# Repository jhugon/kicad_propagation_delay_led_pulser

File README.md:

# Propagation Delay LED Pulser Board in KiCAD

This KiCad board pulses an LED with a very short pulse. The pulse width is
defined by the propagation delay of 3 inverters.

Main power supply: 5 V

LED bias: 0-1.4 V, lower is brighter

## Changelog

- v1.0 Difficult to hand-solder due to heat loss to ground plane (too many vias) and reversed 0612 capacitors
- v1.1 Remove extra vias and switch from 0612 to 1206 coupling caps

## Performance

### v1.1

Measured on 2022-05-04

Current draw not visible on power supply, so less than 10 mA

All measured with a 10x passive oscilloscope probe and ground clib hooked up to coax out:

- The clock coming out of the timer: 9.36 kHz
- The pulse coming out of the NAND gate:
  - Rise and fall times of 2 ns (may be probes)
  - Width of 11 ns
  - Baseline is 4.8 V
  - Pulse is 8 mV
- The pulse coming out of the coax driving inverters, going into R2:
  - A fair amount of ringing ~ 20%
  - Rise and fall times of 2 ns (see above)
  - Width of 11 ns
  - Baseline is -77 mV
  - Pulse is 5 V
- The LED anode:
  - Rise time: 2 ns
  - Fall time: ringing 8.5 ns
  - Width: 12 ns
  - Baseline: -77 mV
  - Pulse: 2.8 V

Pulse measurement of coax output into high-Z scope input:

- Rise time 2.48 ns
- Fall time 2.45 ns
- Width 11.61 ns
- Baseline -90 mV
- Pulse 4.6 V
- Ringing ~ 10%, damped out around 20 ns after pulse fall

LED pulse measurements return a signal as expected at 9.36 kHz. The signal is
controllable with the bias voltage. Noise seems high, but that may be something
else

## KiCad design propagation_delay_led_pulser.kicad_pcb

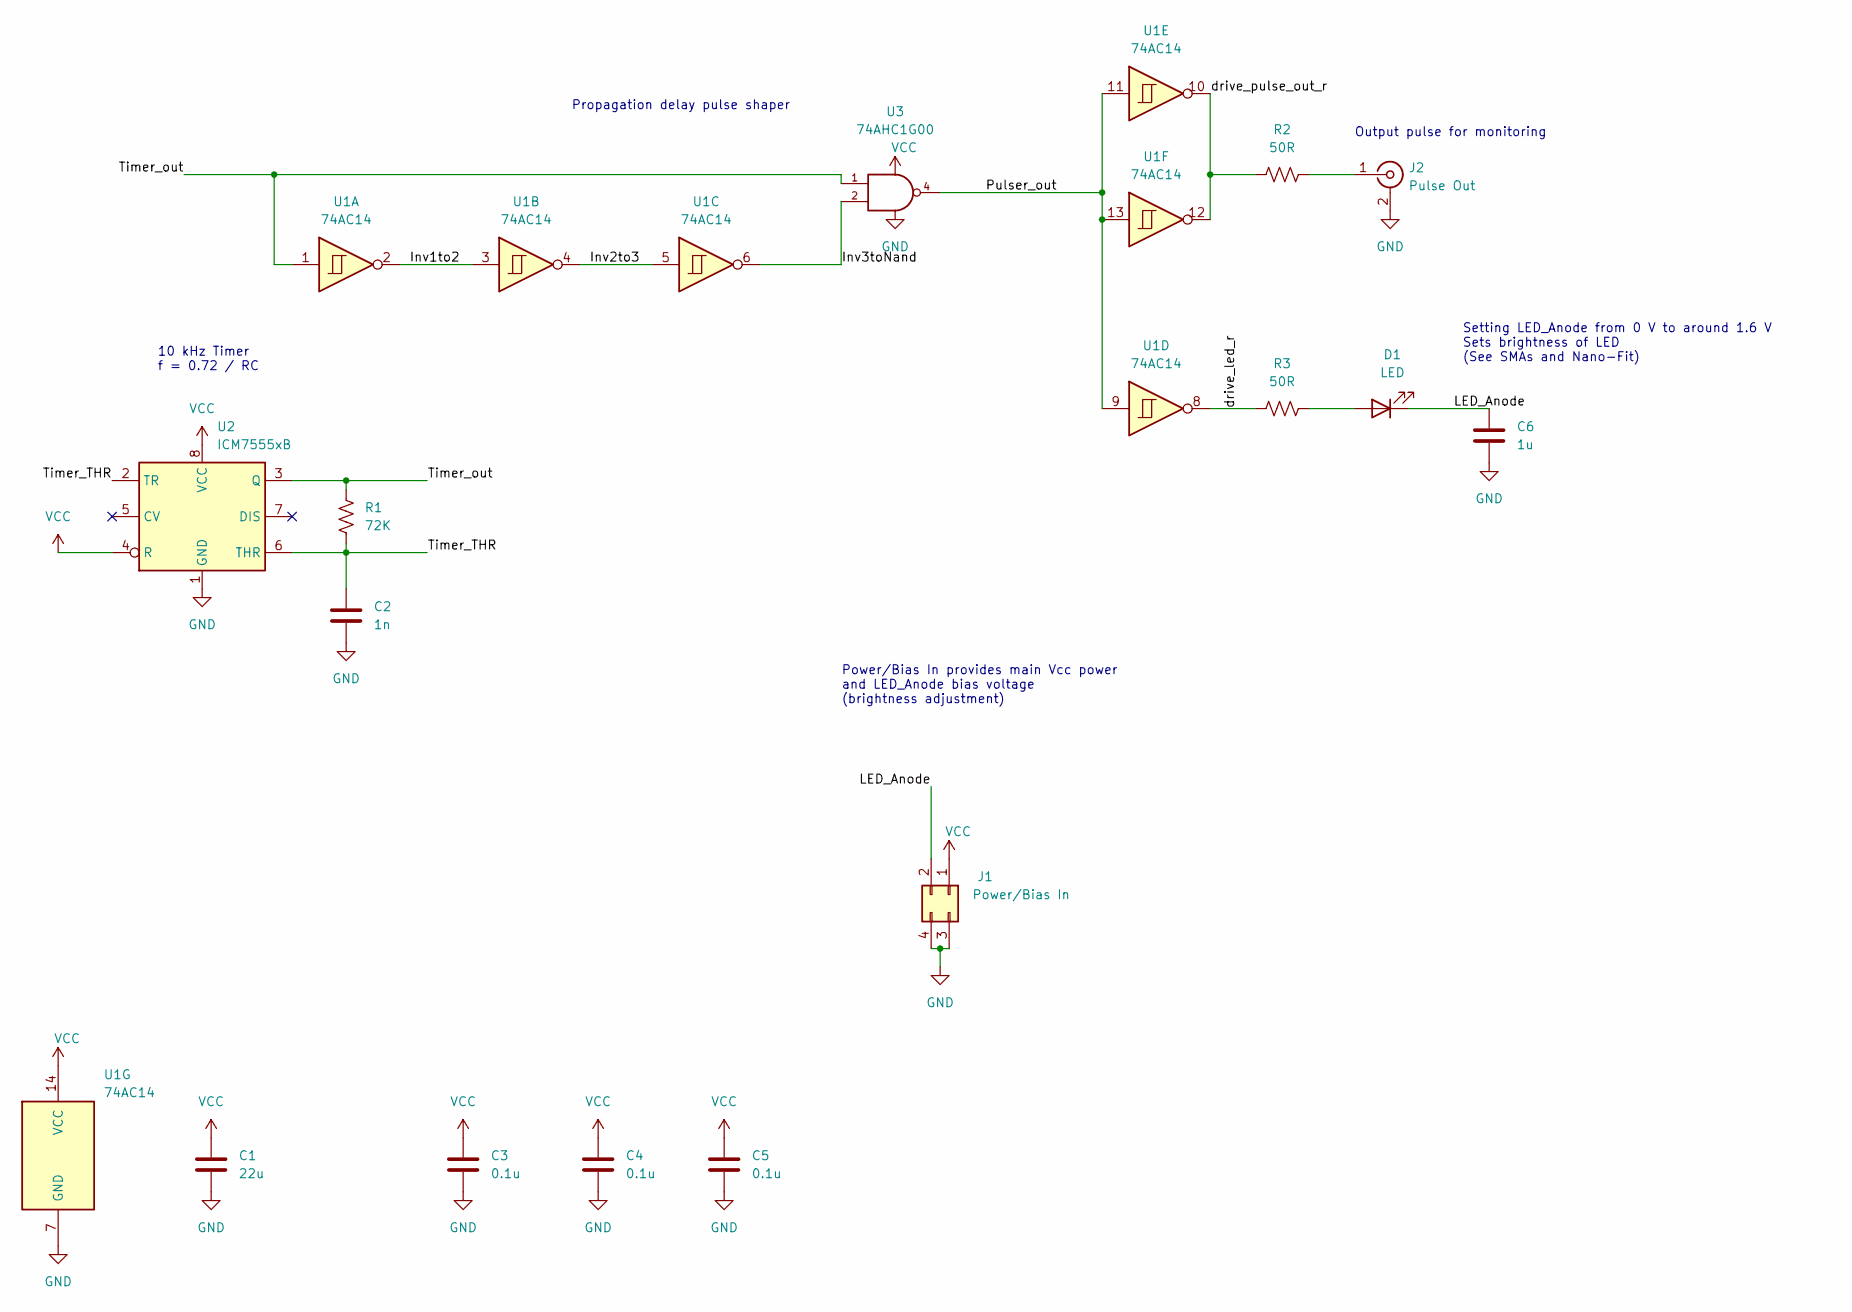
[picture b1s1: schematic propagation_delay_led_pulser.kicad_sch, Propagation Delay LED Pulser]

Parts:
C1: 22u; C_1206_3216Metric_Pad1.33x1.80mm_HandSolder; Part CL31A226KAHNNNE
C2: 1n; C_1206_3216Metric_Pad1.33x1.80mm_HandSolder; Part 12063A102FAT2A
C3, C4, C5: 0.1u; C_1206_3216Metric_Pad1.33x1.80mm_HandSolder; Part CL31B104KBCNNND
C6: 1u; C_1206_3216Metric_Pad1.33x1.80mm_HandSolder; Part CL31B105KBHNFNE
D1: LED; LED_1206_3216Metric_Pad1.42x1.75mm_HandSolder; Part LTST-C150TBKT
J1: Power/Bias In; Molex_Nano-Fit_105314-xx04_2x02_P2.50mm_Horizontal; Part 1053141304
J2: Pulse Out; SMA_Amphenol_132289_EdgeMount; Part 132289
R1: 72K; R_1206_3216Metric_Pad1.30x1.75mm_HandSolder; Part CRCW120671K5FKEA
R2, R3: 50R; R_1206_3216Metric_Pad1.30x1.75mm_HandSolder; Part CRCW120649R9FKEAC
U1: 74AC14; SOIC-14_3.9x8.7mm_P1.27mm; Part SN74AC14D
U2: ICM7555xB; SOIC-8_3.9x4.9mm_P1.27mm; Part ICM7555ESA+
U3: 74AHC1G00; SOT-23-5_HandSoldering; Part SN74AHC1G00DBV

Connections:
/Inv1to2: U1.2, U1.3
/Inv2to3: U1.4, U1.5
/Inv3toNand: U1.6, U3.2
/LED_Anode: C6.1, D1.1 (K), J1.2
/Pulser_out: U1.9, U1.11, U1.13, U3.4
/Timer_THR: C2.1, R1.2, U2.2 (TR), U2.6 (THR)
/Timer_out: R1.1, U1.1, U2.3 (Q), U3.1
/drive_led_r: R3.1, U1.8
/drive_pulse_out_r: R2.1, U1.10, U1.12
GND: C1.2, C2.2, C3.2, C4.2, C5.2, C6.2, J1.3, J1.4, J2.2 (Ext), U1.7 (GND), U2.1 (GND), U3.3 (GND)
unnamed: D1.2 (A), R3.2
unnamed: J2.1 (In), R2.2
VCC: C1.1, C3.1, C4.1, C5.1, J1.1, U1.14 (VCC), U2.4 (R), U2.8 (VCC), U3.5 (VCC)

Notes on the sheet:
Output pulse for monitoring
Setting LED_Anode from 0 V to around 1.6 V Sets brightness of LED (See SMAs and Nano-Fit)
Propagation delay pulse shaper
10 kHz Timer f = 0.72 / RC
Power/Bias In provides main Vcc power and LED_Anode bias voltage (brightness adjustment)

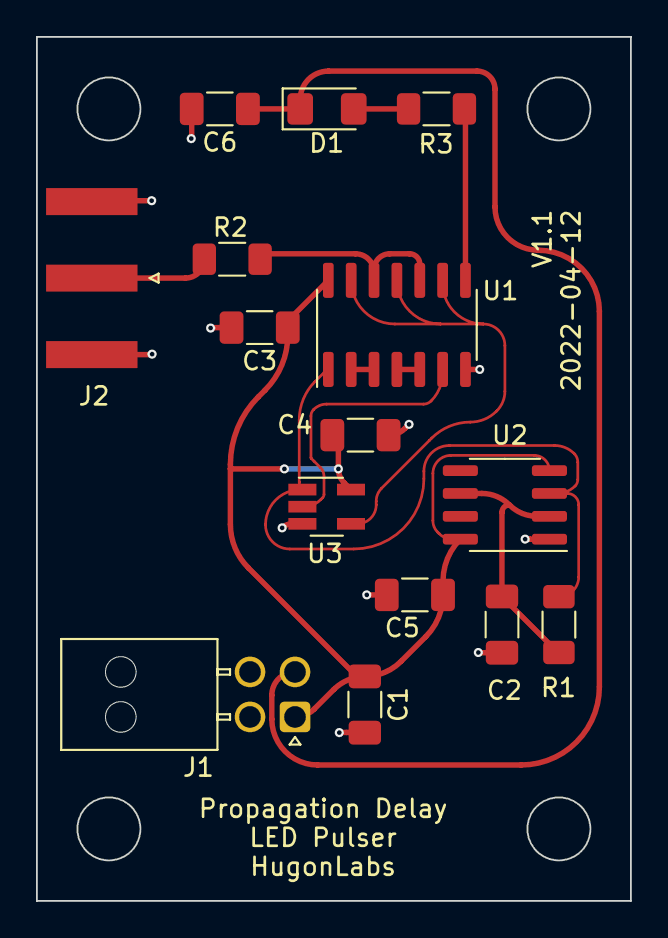
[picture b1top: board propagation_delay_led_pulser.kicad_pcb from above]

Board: 2 copper layers, 33.0 x 48.0 mm, 15 parts (0 on the bottom side), 13 nets.

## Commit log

2022-02-27 Switched to 555 for timer
2022-02-28 Changed headers to one nano-fit
2022-02-28 removed pwr/bias SMAs and initial PCB placement
    also added mfr/part for timer capacitor
2022-02-28 Added board outline
    aligned connectors with outline
    added power for inverter to schematic
2022-02-28 most routing done, need to poar ground plane
2022-02-28 PCB layout complete
2022-02-28 Generated Gerbers for v1
2022-04-12 Removed extra vias and changed 0612 caps to 1206
    should ease soldering greatly
    Hopefully all done for v1.1
2022-04-12 generated v1.1 gerbers
    successfully uploaded to manufacturer
2022-05-04 README: added some performance measurements
2022-05-04 added more performance results
